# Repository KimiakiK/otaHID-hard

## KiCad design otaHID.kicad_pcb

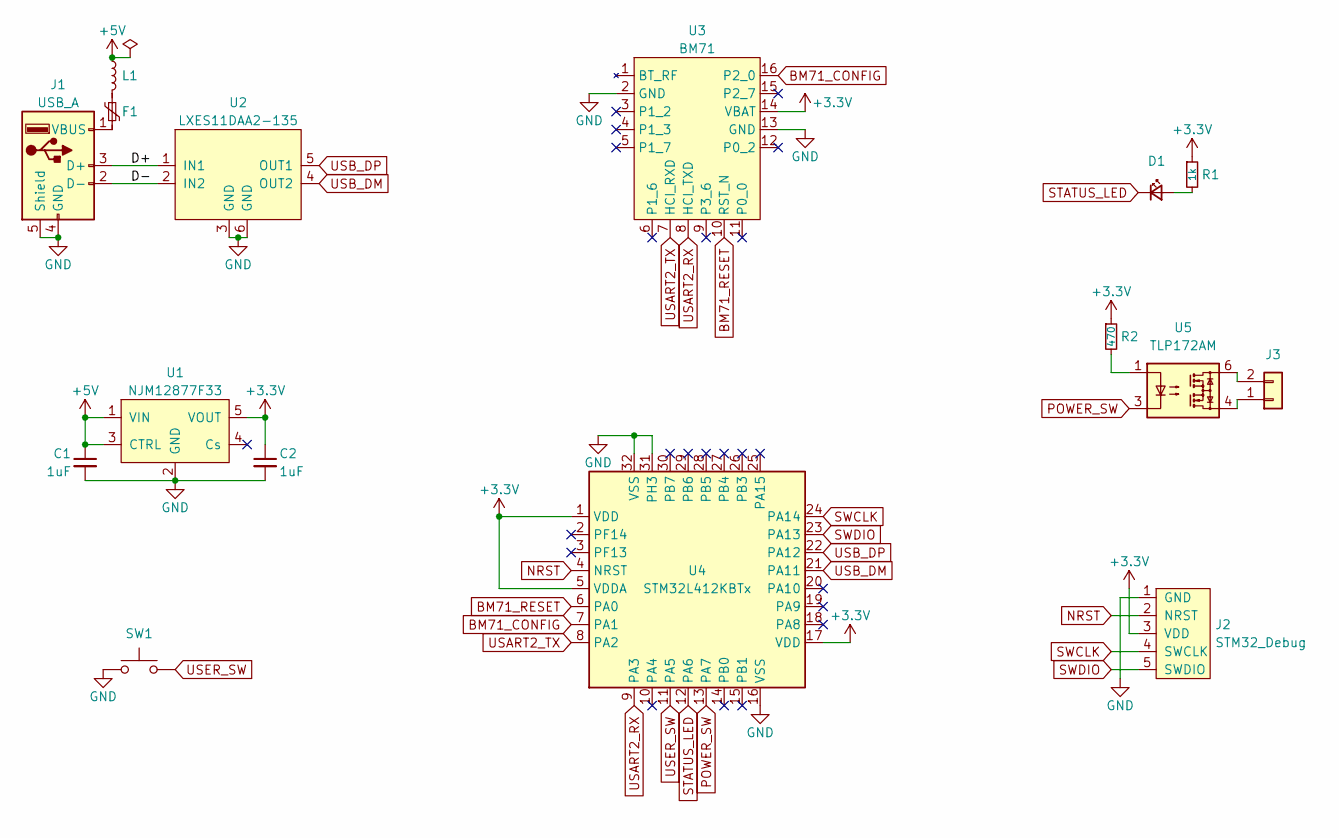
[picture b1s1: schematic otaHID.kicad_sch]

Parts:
C1, C2: 1uF; 1005Metric
D1: LED; 1608Metric
F1: MF-FSMF020X-2; 1608Metric
J1: USB_A; USB Type-A
J2: STM32_Debug; STM32_Debug_5pin
J3: A1001WR-S-2P
L1: BLM18PG600SN1D; 1608Metric
R1: 1k; 1005Metric
R2: 470; 1005Metric
SW1: TVAF06-A020B-R; SideSW_THAF01-NC-R
U1: NJM12877F33; SOT-23-5
U2: LXES11DAA2-135; LXES11D
U3: BM71
U4: STM32L412KBTx; QFN-32-1EP_5x5mm_P0.5mm_EP3.3x3.3mm
U5: TLP172AM; MFSOP6-4_4.4x3.6mm_P1.27mm

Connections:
+3.3V: C2.1, J2.3 (VDD), R1.1, R2.1, U1.5 (VOUT), U3.14 (VBAT), U4.1 (VDD), U4.5 (VDDA), U4.17 (VDD)
+5V: C1.1, L1.1, U1.1 (VIN), U1.3 (CTRL)
/D+: J1.3 (D+), U2.1 (IN1)
/D-: J1.2 (D-), U2.2 (IN2)
BM71_CONFIG: U3.16 (P2_0), U4.7 (PA1)
BM71_RESET: U3.10 (RST_N), U4.6 (PA0)
GND: C1.2, C2.2, J1.4 (GND), J1.5 (Shield), J2.1 (GND), SW1.2, U1.2 (GND), U2.3 (GND), U2.6 (GND), U3.2 (GND), U3.13 (GND), U4.16 (VSS), U4.31 (PH3), U4.32 (VSS)
NRST: J2.2 (NRST), U4.4 (NRST)
unnamed: D1.2 (A), R1.2
unnamed: F1.1, L1.2
unnamed: F1.2, J1.1 (VBUS)
unnamed: J3.1, U5.4
unnamed: J3.2, U5.6
unnamed: R2.2, U5.1
POWER_SW: U4.13 (PA7), U5.3
STATUS_LED: D1.1 (K), U4.12 (PA6)
SWCLK: J2.4 (SWCLK), U4.24 (PA14)
SWDIO: J2.5 (SWDIO), U4.23 (PA13)
USART2_RX: U3.8 (HCI_TXD), U4.9 (PA3)
USART2_TX: U3.7 (HCI_RXD), U4.8 (PA2)
USB_DM: U2.4 (OUT2), U4.21 (PA11)
USB_DP: U2.5 (OUT1), U4.22 (PA12)
USER_SW: SW1.1, U4.11 (PA5)

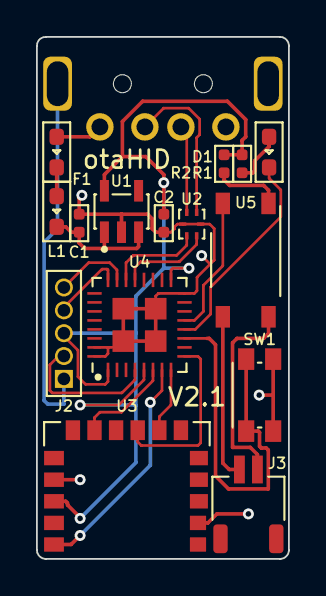
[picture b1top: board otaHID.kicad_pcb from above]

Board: 2 copper layers, 14.0 x 29.0 mm, 16 parts (1 on the bottom side), 23 nets.

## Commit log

2022-03-31 基板 V1.0
2022-12-10 基盤v2.0
2023-01-08 基板 V2.1
